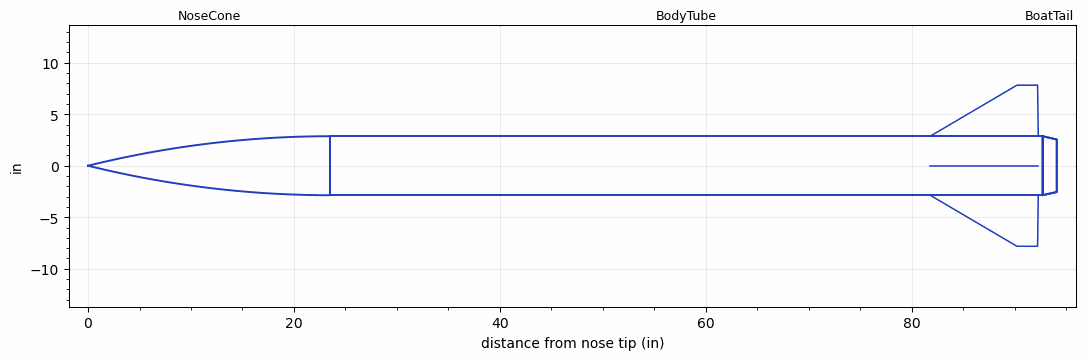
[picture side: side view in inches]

<RASAeroDocument>
 <FileVersion>2</FileVersion>
 <RocketDesign>
  <NoseCone>
   <Length>23.5</Length>
   <Diameter>5.73</Diameter>
   <Shape>Tangent Ogive</Shape>
   <Location>0</Location>
  </NoseCone>
  <BodyTube>
   <Length>69.215</Length>
   <Diameter>5.73</Diameter>
   <Location>23.5</Location>
   <BoattailLength>1.377</BoattailLength>
   <BoattailRearDiameter>5.1</BoattailRearDiameter>
   <Fin>
    <Count>4</Count>
    <Chord>10.5</Chord>
    <Span>4.96</Span>
    <SweepDistance>8.4331</SweepDistance>
    <TipChord>2</TipChord>
    <Thickness>0.5617</Thickness>
    <Location>10.92</Location>
    <AirfoilSection>Double Wedge</AirfoilSection>
    <FX1>3.125</FX1>
   </Fin>
  </BodyTube>
  <BoatTail>
   <Length>1.377</Length>
   <Diameter>5.73</Diameter>
   <RearDiameter>5.1</RearDiameter>
   <Location>92.715</Location>
  </BoatTail>
  <Surface>Camouflage Paint</Surface>
  <ModifiedBarrowman>False</ModifiedBarrowman>
  <Turbulence>False</Turbulence>
  <UseBooster1>False</UseBooster1>
  <UseBooster2>False</UseBooster2>
 </RocketDesign>
 <LaunchSite>
  <Altitude>1214</Altitude>
  <Pressure>28.64</Pressure>
  <RodAngle>6</RodAngle>
  <RodLength>15</RodLength>
  <Temperature>68</Temperature>
  <WindSpeed>15.35</WindSpeed>
 </LaunchSite>
 <Recovery>
  <Altitude1>656.168</Altitude1>
  <Altitude2>1500</Altitude2>
  <DeviceType1>Parachute</DeviceType1>
  <DeviceType2>Parachute</DeviceType2>
  <Event1>True</Event1>
  <Event2>True</Event2>
  <Size1>31.8897</Size1>
  <Size2>158.2674</Size2>
  <EventType1>Apogee</EventType1>
  <EventType2>Altitude</EventType2>
  <CD1>1.5</CD1>
  <CD2>0</CD2>
 </Recovery>
 <SimulationList>
  <Simulation>
   <SustainerEngine>N2540-GR-P  (CTI)</SustainerEngine>
   <SustainerLaunchWt>56.23</SustainerLaunchWt>
   <SustainerNozzleDiameter>2.37</SustainerNozzleDiameter>
   <SustainerCG>60.36</SustainerCG>
   <SustainerIgnitionDelay>0</SustainerIgnitionDelay>
   <Booster1SeparationDelay>0</Booster1SeparationDelay>
   <Booster1IgnitionDelay>0</Booster1IgnitionDelay>
   <IncludeBooster1>False</IncludeBooster1>
   <Booster2Delay>0</Booster2Delay>
   <IncludeBooster2>False</IncludeBooster2>
   <TimetoApogee>38.35957</TimetoApogee>
   <MaxAltitude>28418.78</MaxAltitude>
   <MaxVelocity>2117.339</MaxVelocity>
  </Simulation>
  <Simulation>
   <SustainerLaunchWt>65.9603</SustainerLaunchWt>
   <SustainerCG>65.3991</SustainerCG>
   <SustainerIgnitionDelay>0</SustainerIgnitionDelay>
   <Booster1SeparationDelay>0</Booster1SeparationDelay>
   <Booster1IgnitionDelay>0</Booster1IgnitionDelay>
   <IncludeBooster1>False</IncludeBooster1>
   <Booster2Delay>0</Booster2Delay>
   <IncludeBooster2>False</IncludeBooster2>
  </Simulation>
  <Simulation>
   <SustainerLaunchWt>64.7224</SustainerLaunchWt>
   <SustainerCG>65.2686</SustainerCG>
   <SustainerIgnitionDelay>0</SustainerIgnitionDelay>
   <Booster1SeparationDelay>0</Booster1SeparationDelay>
   <Booster1IgnitionDelay>0</Booster1IgnitionDelay>
   <IncludeBooster1>False</IncludeBooster1>
   <Booster2Delay>0</Booster2Delay>
   <IncludeBooster2>False</IncludeBooster2>
  </Simulation>
  <Simulation>
   <SustainerLaunchWt>55.8785</SustainerLaunchWt>
   <SustainerCG>66.1409</SustainerCG>
   <SustainerIgnitionDelay>0</SustainerIgnitionDelay>
   <Booster1SeparationDelay>0</Booster1SeparationDelay>
   <Booster1IgnitionDelay>0</Booster1IgnitionDelay>
   <IncludeBooster1>False</IncludeBooster1>
   <Booster2Delay>0</Booster2Delay>
   <IncludeBooster2>False</IncludeBooster2>
  </Simulation>
 </SimulationList>
</RASAeroDocument>
